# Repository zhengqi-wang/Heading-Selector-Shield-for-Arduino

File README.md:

# Heading-Selector-Shield-for-Arduino
Arduino shield as a heading selector for flight simulator games. Can be also used as course selector or other applications.

Not for aviation training purpose! Use at your own risk.

Full HDG selecter functionality can be achieved in FS2020.

SimHDG.ino is the main source file. It is used with FS2020 to Arduino. https://github.com/Seahawk240/Microsoft-FS2020-To-Arduino 

SimInterfaceHDGv2.ino is a test file. The encoder controls the display value from 000 to 999.

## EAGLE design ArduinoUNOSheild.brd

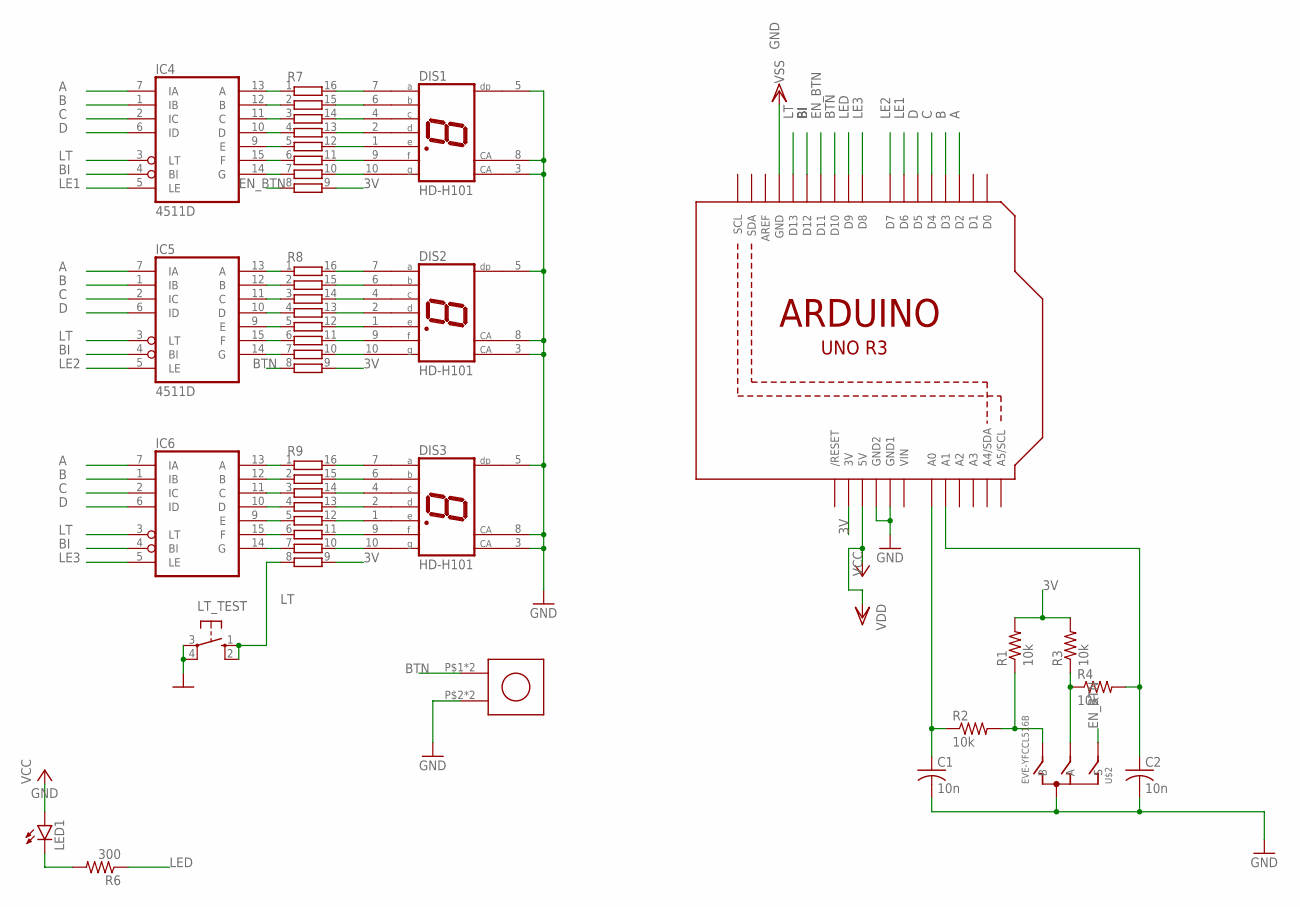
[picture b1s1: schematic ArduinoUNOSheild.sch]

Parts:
C1, C2: 10n; C0603
DIS1, DIS2, DIS3: HD-H101; HDSP-M
IC4, IC5, IC6: 4511D; SO16
LED1: LEDCHIP-LED0805; CHIP-LED0805
LT_TEST: 10-XX; B3F-10XX
R1, R2, R3, R4: 10k; R0603
R6: 300; R0603
R7, R8, R9: 4816P-T01; 4816P
U1: ARDUINOR3-NOIOREF-NOTEXT; ARDUINOR3-NOTEXT-NOIOREF
U$1: AE1027; BUTTON5X13MM
U$2: EVE-YFCCL516B; PANASONIC_EVE_Y

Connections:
3V: R1.2, R3.2, R7.9, R8.9, R9.9, U1.3V
A: IC4.7 (IA), IC5.7 (IA), IC6.7 (IA), U1.D2
A1: C2.1, R4.2, U1.A1
B: IC4.1 (IB), IC5.1 (IB), IC6.1 (IB), U1.D3
BI: IC4.4 (BI), IC5.4 (BI), IC6.4 (BI), U1.D12
BTN: R8.8, U1.D10, U$1.P$1, U$1.P$11
C: IC4.2 (IC), IC5.2 (IC), IC6.2 (IC), U1.D4
D: IC4.6 (ID), IC5.6 (ID), IC6.6 (ID), U1.D5
EN_BTN: R7.8, U1.D11, U$2.S
GND: C1.2, C2.2, DIS1.3 (CA), DIS1.5 (DP), DIS1.8 (CA), DIS2.3 (CA), DIS2.5 (DP), DIS2.8 (CA), DIS3.3 (CA), DIS3.5 (DP), DIS3.8 (CA), IC4.8 (VSS), IC5.8 (VSS), IC6.8 (VSS), LT_TEST.3, LT_TEST.4 (P1), U1.GND, U1.GND1, U1.GND2, U$1.P$2, U$1.P$12, U$2.COM (C), U$2.GND (C), U$2.GND1 (C)
LE1: IC4.5 (LE), U1.D6
LE2: IC5.5 (LE), U1.D7
LE3: IC6.5 (LE), U1.D8
LED: R6.1, U1.D9
LED_N: LED1.C, R6.2
LT: IC4.3 (LT), IC5.3 (LT), IC6.3 (LT), LT_TEST.1 (S), LT_TEST.2 (S1), R9.8, U1.D13
unnamed: DIS1.7 (A), R7.16
unnamed: DIS1.6 (B), R7.15
unnamed: DIS1.4 (C), R7.14
unnamed: DIS1.2 (D), R7.13
unnamed: DIS1.1 (E), R7.12
unnamed: DIS1.9 (F), R7.11
unnamed: DIS1.10 (G), R7.10
unnamed: DIS2.7 (A), R8.16
unnamed: DIS2.6 (B), R8.15
unnamed: DIS2.4 (C), R8.14
unnamed: DIS2.2 (D), R8.13
unnamed: DIS2.1 (E), R8.12
unnamed: DIS2.9 (F), R8.11
unnamed: DIS2.10 (G), R8.10
unnamed: DIS3.7 (A), R9.16
unnamed: DIS3.6 (B), R9.15
unnamed: DIS3.4 (C), R9.14
unnamed: DIS3.2 (D), R9.13
unnamed: DIS3.1 (E), R9.12
unnamed: DIS3.9 (F), R9.11
unnamed: DIS3.10 (G), R9.10
unnamed: R1.1, R2.2, U$2.B, U$2.B1 (B)
unnamed: C1.1, R2.1, U1.A0
unnamed: R3.1, R4.1, U$2.A
unnamed: IC4.13 (A), R7.1
unnamed: IC4.12 (B), R7.2
unnamed: IC4.11 (C), R7.3
unnamed: IC4.10 (D), R7.4
unnamed: IC4.9 (E), R7.5
unnamed: IC4.15 (F), R7.6
unnamed: IC4.14 (G), R7.7
unnamed: IC5.13 (A), R8.1
unnamed: IC5.12 (B), R8.2
unnamed: IC5.11 (C), R8.3
unnamed: IC5.10 (D), R8.4
unnamed: IC5.9 (E), R8.5
unnamed: IC5.15 (F), R8.6
unnamed: IC5.14 (G), R8.7
unnamed: IC6.13 (A), R9.1
unnamed: IC6.12 (B), R9.2
unnamed: IC6.11 (C), R9.3
unnamed: IC6.10 (D), R9.4
unnamed: IC6.9 (E), R9.5
unnamed: IC6.15 (F), R9.6
unnamed: IC6.14 (G), R9.7
VCC: IC4.16 (VDD), IC5.16 (VDD), IC6.16 (VDD), LED1.A, U1.5V
VIN: U1.VIN

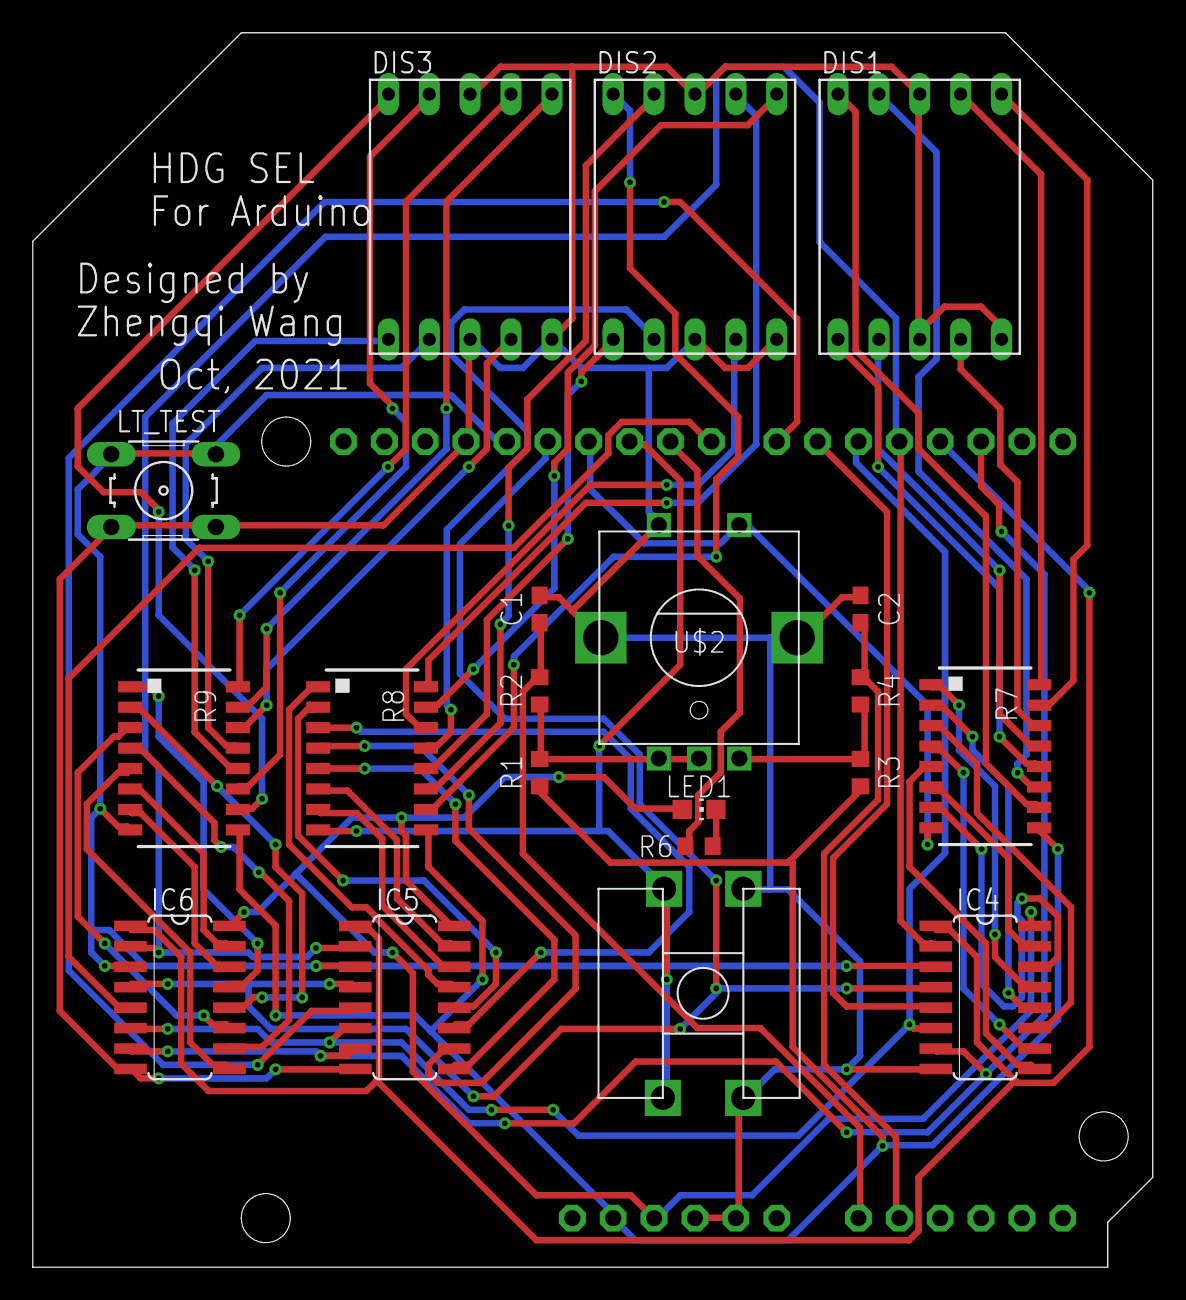
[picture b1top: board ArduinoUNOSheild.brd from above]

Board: 2 copper layers, 69.6 x 76.7 mm, 21 parts (0 on the bottom side), 62 nets.
